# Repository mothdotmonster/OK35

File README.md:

***

35-key half-keyboard PCB, designed to be used in pairs

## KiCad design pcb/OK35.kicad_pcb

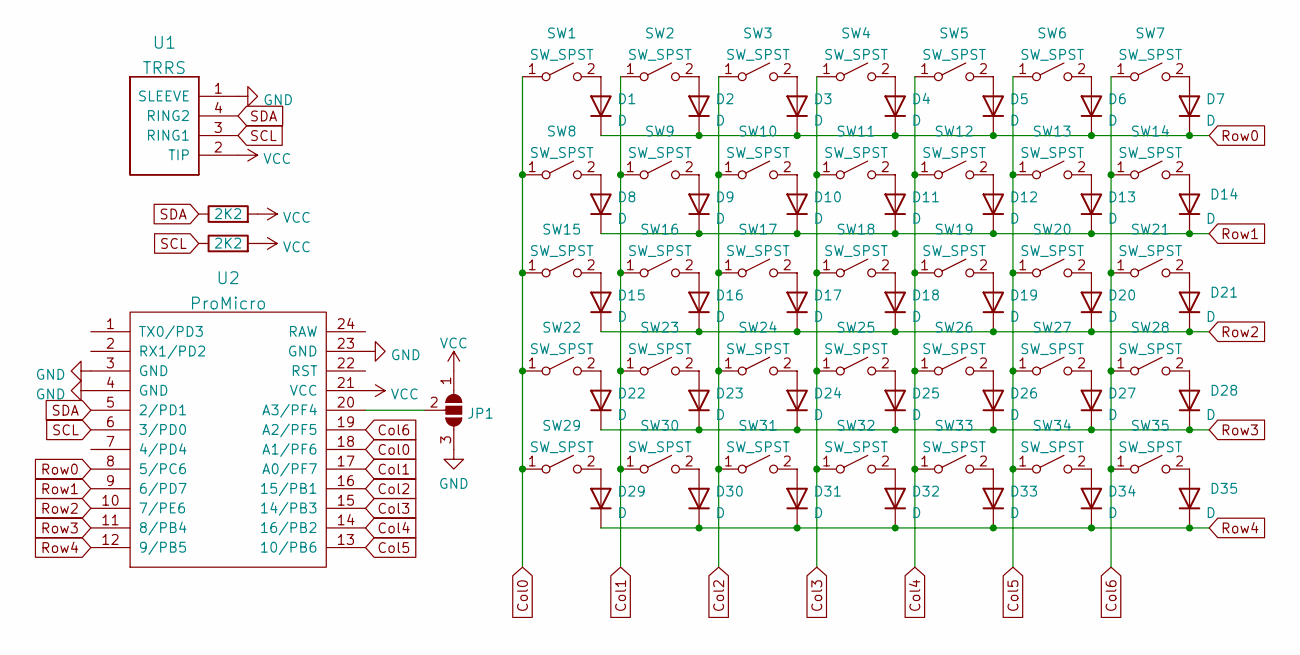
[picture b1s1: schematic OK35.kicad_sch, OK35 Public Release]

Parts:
D1, D2, D3, D4, D5, D6, D7, D8, D9, D10, D11, D12, D13, D14, D15, D16, D17, D18, D19, D20, D21, D22, D23, D24, D25, D26, D27, D28, D29, D30, D31, D32, D33, D34, D35: D; MD_Diode
JP1: SolderJumper_3_Open; SolderJumper-3_P2.0mm_Open_TrianglePad1.0x1.5mm
R1, R2: 2K2; R_Axial_DIN0207_L6.3mm_D2.5mm_P7.62mm_Horizontal
SW1, SW2, SW3, SW4, SW5, SW6, SW7, SW8, SW9, SW10, SW11, SW12, SW13, SW14, SW15, SW16, SW17, SW18, SW19, SW20, SW21, SW22, SW23, SW24, SW25, SW26, SW27, SW28, SW29, SW30, SW31, SW32, SW33, SW34, SW35: SW_SPST; MX-Alps-Choc-1U-NoLED
U1: TRRS; TRRS-PJ-320A
U2: ProMicro; ArduinoProMicro-ZigZag

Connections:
Col0: SW1.1 (A), SW8.1 (A), SW15.1 (A), SW22.1 (A), SW29.1 (A), U2.18 (A1/PF6)
Col1: SW2.1 (A), SW9.1 (A), SW16.1 (A), SW23.1 (A), SW30.1 (A), U2.17 (A0/PF7)
Col2: SW3.1 (A), SW10.1 (A), SW17.1 (A), SW24.1 (A), SW31.1 (A), U2.16 (15/PB1)
Col3: SW4.1 (A), SW11.1 (A), SW18.1 (A), SW25.1 (A), SW32.1 (A), U2.15 (14/PB3)
Col4: SW5.1 (A), SW12.1 (A), SW19.1 (A), SW26.1 (A), SW33.1 (A), U2.14 (16/PB2)
Col5: SW6.1 (A), SW13.1 (A), SW20.1 (A), SW27.1 (A), SW34.1 (A), U2.13 (10/PB6)
Col6: SW7.1 (A), SW14.1 (A), SW21.1 (A), SW28.1 (A), SW35.1 (A), U2.19 (A2/PF5)
GND: JP1.3 (B), U1.1 (SLEEVE), U2.3 (GND), U2.4 (GND), U2.23 (GND)
unnamed: D1.2 (A), SW1.2 (B)
unnamed: D2.2 (A), SW2.2 (B)
unnamed: D3.2 (A), SW3.2 (B)
unnamed: D4.2 (A), SW4.2 (B)
unnamed: D5.2 (A), SW5.2 (B)
unnamed: D6.2 (A), SW6.2 (B)
unnamed: D7.2 (A), SW7.2 (B)
unnamed: D8.2 (A), SW8.2 (B)
unnamed: D9.2 (A), SW9.2 (B)
unnamed: D10.2 (A), SW10.2 (B)
unnamed: D11.2 (A), SW11.2 (B)
unnamed: D12.2 (A), SW12.2 (B)
unnamed: D13.2 (A), SW13.2 (B)
unnamed: D14.2 (A), SW14.2 (B)
unnamed: D15.2 (A), SW15.2 (B)
unnamed: D16.2 (A), SW16.2 (B)
unnamed: D17.2 (A), SW17.2 (B)
unnamed: D18.2 (A), SW18.2 (B)
unnamed: D19.2 (A), SW19.2 (B)
unnamed: D20.2 (A), SW20.2 (B)
unnamed: D21.2 (A), SW21.2 (B)
unnamed: D22.2 (A), SW22.2 (B)
unnamed: D23.2 (A), SW23.2 (B)
unnamed: D24.2 (A), SW24.2 (B)
unnamed: D25.2 (A), SW25.2 (B)
unnamed: D26.2 (A), SW26.2 (B)
unnamed: D27.2 (A), SW27.2 (B)
unnamed: D28.2 (A), SW28.2 (B)
unnamed: D29.2 (A), SW29.2 (B)
unnamed: D30.2 (A), SW30.2 (B)
unnamed: D31.2 (A), SW31.2 (B)
unnamed: D32.2 (A), SW32.2 (B)
unnamed: D33.2 (A), SW33.2 (B)
unnamed: D34.2 (A), SW34.2 (B)
unnamed: D35.2 (A), SW35.2 (B)
unnamed: JP1.2 (C), U2.20 (A3/PF4)
Row0: D1.1 (K), D2.1 (K), D3.1 (K), D4.1 (K), D5.1 (K), D6.1 (K), D7.1 (K), U2.8 (5/PC6)
Row1: D8.1 (K), D9.1 (K), D10.1 (K), D11.1 (K), D12.1 (K), D13.1 (K), D14.1 (K), U2.9 (6/PD7)
Row2: D15.1 (K), D16.1 (K), D17.1 (K), D18.1 (K), D19.1 (K), D20.1 (K), D21.1 (K), U2.10 (7/PE6)
Row3: D22.1 (K), D23.1 (K), D24.1 (K), D25.1 (K), D26.1 (K), D27.1 (K), D28.1 (K), U2.11 (8/PB4)
Row4: D29.1 (K), D30.1 (K), D31.1 (K), D32.1 (K), D33.1 (K), D34.1 (K), D35.1 (K), U2.12 (9/PB5)
SCL: R2.1, U1.3 (RING1), U2.6 (3/PD0)
SDA: R1.1, U1.4 (RING2), U2.5 (2/PD1)
VCC: JP1.1 (A), R1.2, R2.2, U1.2 (TIP), U2.21 (VCC)

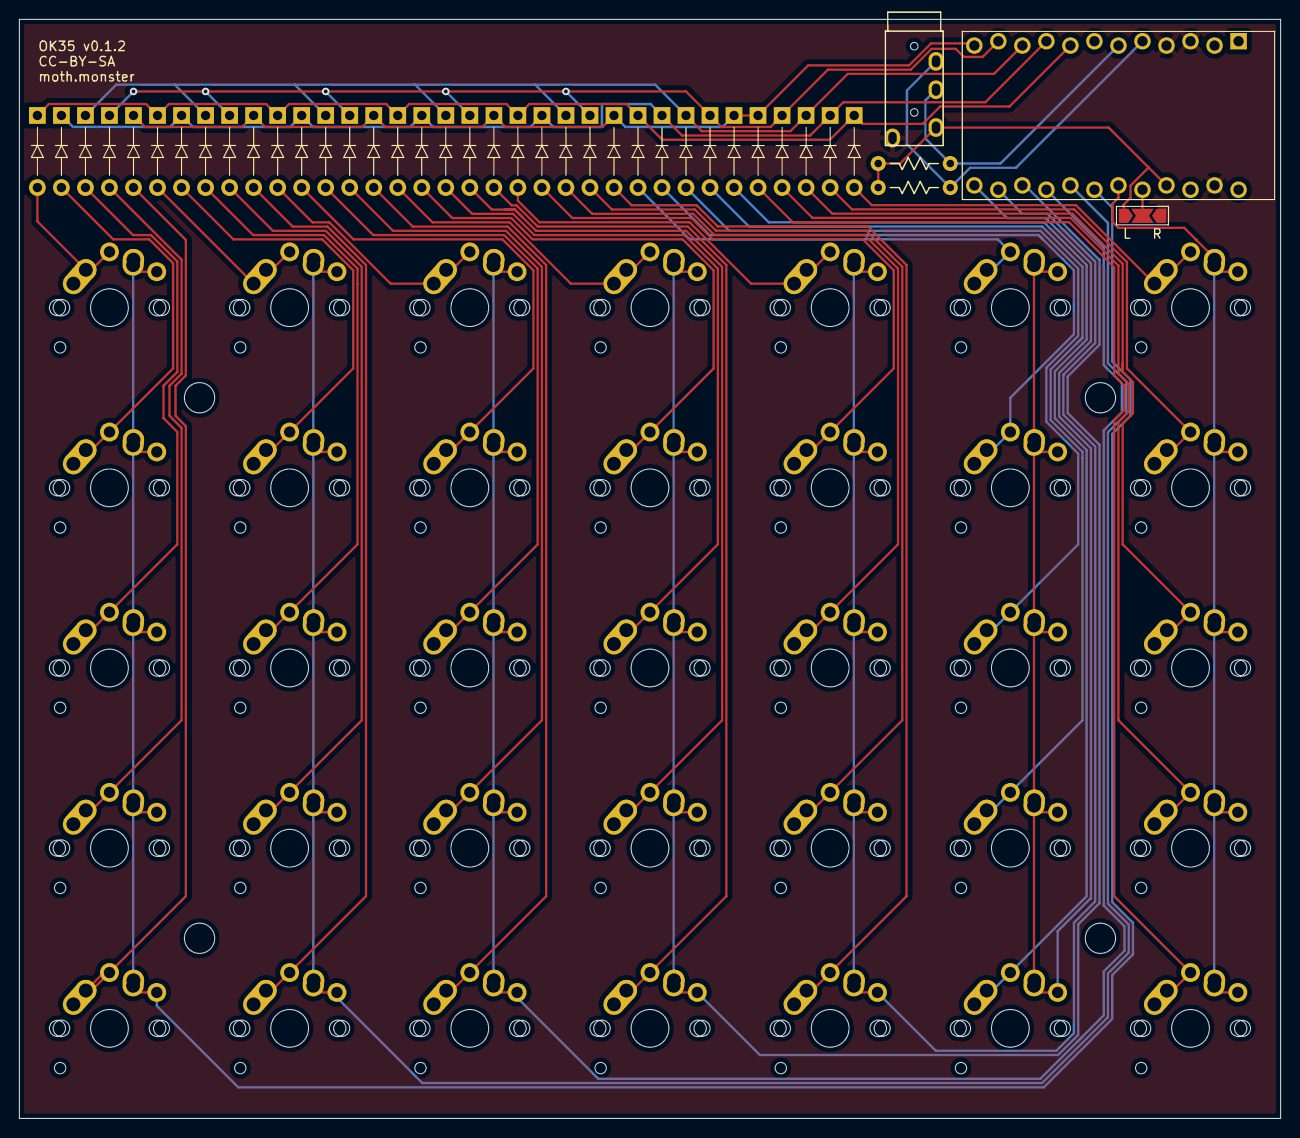
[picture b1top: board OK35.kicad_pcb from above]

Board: 2 copper layers, 133.3 x 116.2 mm, 75 parts (0 on the bottom side), 52 nets.

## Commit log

2022-02-19 v0.1.0 initial commit
2022-02-19 license
2022-02-19 images
2022-02-21 v0.1.1 - fixing noob mistakes
2022-02-21 cleanup some stuff
2022-02-23 3d printable case
2022-03-06 real life pic
2022-03-06 reorganize
2022-03-06 reorganize?
2022-03-06 v0.1.2 - add handedness jumper
2022-03-07 v0.1.3 - standard 2u switch options
2022-03-07 simplify foot
2022-03-09 v0.1.3b - moved some holes
2022-03-09 Revert "v0.1.3b - moved some holes"
    This reverts commit e650355a7cdd176761959e97b09434696344432b.
2022-03-09 Revert "simplify foot"
    This reverts commit dd490eab3f5aa29ff72f52f891d52c202795291a.
2022-03-09 v0.1.3 was bad
    This reverts commit 27f9da0c8f8c043d86356701b4d41a0e5f33df05.
2022-03-09 put the simplifed foot back
2022-03-10 v0.1.2 finalized public release
2022-03-11 number mistake

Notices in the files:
pcb/OK35.kicad_pcb:
CC-BY-SA
